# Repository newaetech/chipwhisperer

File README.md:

# ChipWhisperer

## Important Links

[Documentation](https://chipwhisperer.readthedocs.io/en/sca101/index.html) | [Labs](https://github.com/newaetech/chipwhisperer-jupyter/tree/sca101) | [Forum](http://forum.newae.com) | [Store](https://store.newae.com) | [NewAE](http://newae.com)

## ChipWhisperer 7.0: Revamped Analyzer, Project, SCA101

ChipWhisperer 7.0 is bringing major improvements to projects, analyzer, as well as a new online course, SCA101. These changes include:

* New Zarr based projects with improved functionality over previous projects
* New CPA attack class with major performance improvements
* Better results API for CPA attacks
* Simplification for project/analyzer API
* Use of integer math throughout the project
* Removal of unmaintained parts of Analyzer
* Porting of MixColumns attack to Analyzer
* Iterators for KTP classes

We also have a more thorough [document of changes](https://docs.google.com/document/d/1KBrlV3X3fyg3PniKdv6pZg0s0MAX2dzbSdZiwbm_nh4/edit?usp=sharing).

The [SCA101 Online course](https://learn.chipwhisperer.io/courses/sca101) is available at [learn.chipwhisperer.io](https://learn.chipwhisperer.io).

**If you need to use ChipWhisperer with the previous API, the final commit with that is available as tag v6.1.0**

## What is ChipWhisperer?

ChipWhisperer is an open source toolchain dedicated to hardware security research. This toolchain consists of several layers of open source components:
* __Hardware__: The ChipWhisperer uses a _capture_ board and a _target_ board. Schematics and PCB layouts for the ChipWhisperer-Husky capture board and a number of target boards are freely available.
* __Firmware__: Three separate pieces of firmware are used on the ChipWhisperer hardware. The capture board has a USB controller (in C) and an FPGA for high-speed captures (in Verilog) with open-source firmware. Also, the target device has its own firmware; this repository includes many firmware examples for different targets.
* __Software__: The ChipWhisperer software includes a Python API for talking to ChipWhisperer hardware (ChipWhisperer Capture) and a Python API 
for processing power traces from ChipWhisperer hardware (ChipWhisperer Analyzer). 

You'll find documentation for all of the above [here](https://chipwhisperer.readthedocs.io/en/develop/index.html).

## Getting Started
First time using ChipWhisperer? Go to our new [documentation site](https://chipwhisperer.readthedocs.io/en/develop/index.html) for all you need to know to get started with ChipWhisperer.

## Help!
Stuck? If you need a hand, there are a few places you can ask for help:
* The [NewAE Forum](https://forum.newae.com/) is full of helpful people that can point you in the right direction
* If you find a bug, let us know through the [issue tracker](https://github.com/newaetech/chipwhisperer/issues)

---

ChipWhisperer is a trademark of NewAE Technology Inc., registered in the US, Europe, and China.

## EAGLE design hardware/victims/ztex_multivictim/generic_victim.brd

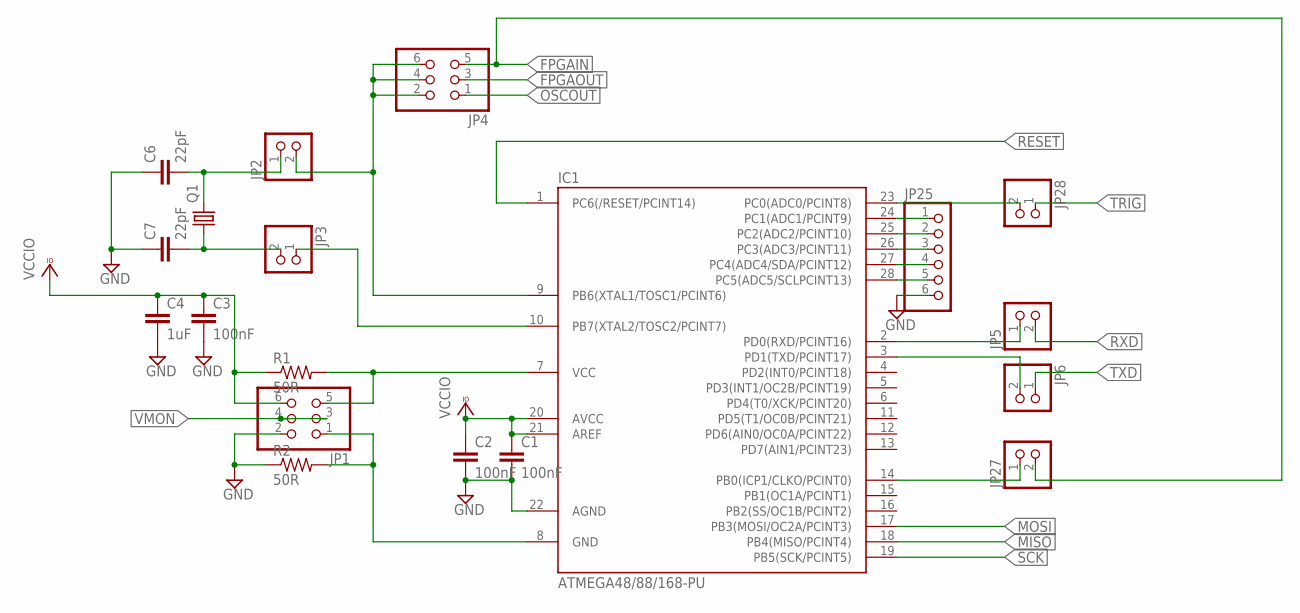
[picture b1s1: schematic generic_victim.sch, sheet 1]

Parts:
C1, C2, C3: 100nF; C0805
C4: 1uF; C0805
C6, C7: 22pF; C0805
IC1: ATMEGA48/88/168-PU; DIL28-3
JP1, JP4: PINHD-2X3; 2X03
JP2, JP3, JP5, JP6, JP27, JP28: PINHD-1X2; 1X02
JP25: PINHD-1X6; 1X06
Q1: CRYSTALHC49U70; HC49U70
R1, R2: 50R; R0805

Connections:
FPGAIN: JP4.5, JP27.2; also elsewhere on the board
FPGAOUT: JP4.3; also elsewhere on the board
GND: C1.2, C2.2, C3.2, C4.2, C6.1, C7.1, IC1.22 (AGND), JP1.2, JP25.6, R2.1; also elsewhere on the board
MISO: IC1.18 (PB4(MISO/PCINT4)); also elsewhere on the board
MOSI: IC1.17 (PB3(MOSI/OC2A/PCINT3)); also elsewhere on the board
unnamed: IC1.7 (VCC), JP1.5, R1.2
unnamed: IC1.8 (GND), JP1.1, R2.2
unnamed: IC1.10 (PB7(XTAL2/TOSC2/PCINT7)), JP3.1
unnamed: C7.2, JP3.2, Q1.1
unnamed: C6.2, JP2.1, Q1.2
unnamed: IC1.14 (PB0(ICP1/CLKO/PCINT0)), JP27.1
unnamed: IC1.2 (PD0(RXD/PCINT16)), JP5.1
unnamed: IC1.3 (PD1(TXD/PCINT17)), JP6.2
unnamed: IC1.9 (PB6(XTAL1/TOSC1/PCINT6)), JP2.2, JP4.2, JP4.4, JP4.6
unnamed: IC1.24 (PC1(ADC1/PCINT9)), JP25.1
unnamed: IC1.25 (PC2(ADC2/PCINT10)), JP25.2
unnamed: IC1.26 (PC3(ADC3/PCINT11)), JP25.3
unnamed: IC1.27 (PC4(ADC4/SDA/PCINT12)), JP25.4
unnamed: IC1.28 (PC5(ADC5/SCLPCINT13)), JP25.5
unnamed: IC1.23 (PC0(ADC0/PCINT8)), JP28.2
OSCOUT: JP4.1; also elsewhere on the board
RESET: IC1.1 (PC6(/RESET/PCINT14)); also elsewhere on the board
RXD: JP5.2; also elsewhere on the board
SCK: IC1.19 (PB5(SCK/PCINT5)); also elsewhere on the board
TRIG: JP28.1; also elsewhere on the board
TXD: JP6.1; also elsewhere on the board
VCCIO: C1.1, C2.1, C3.1, C4.1, IC1.20 (AVCC), IC1.21 (AREF), JP1.6, R1.1; also elsewhere on the board
VMON: JP1.3, JP1.4; also elsewhere on the board

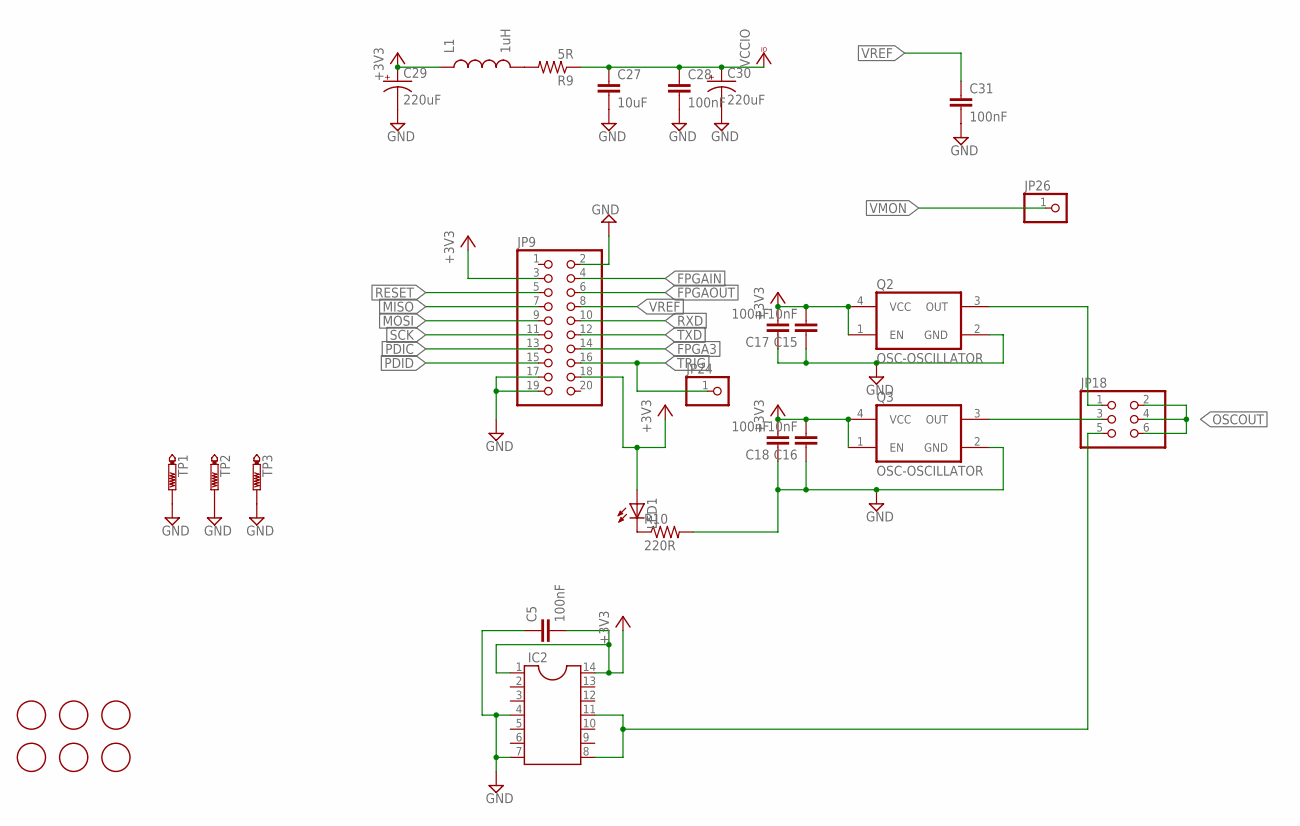
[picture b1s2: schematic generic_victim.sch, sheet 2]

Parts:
C5, C28, C31: 100nF; C0805
C15, C16: 10nF; C0603
C17, C18: 100nF; C0603
C27: 10uF; C0805
C29, C30: 220uF; E3,5-8
IC2: DIL14S; SOCKET-14
JP9: PINHD-2X10; 2X10
JP18: PINHD-2X3; 2X03
JP24, JP26: PINHD-1X1; 1X01
L1: 1uH; 0805
LED1: LED3MM
Q2, Q3: OSC-OSCILLATOR; OSCILLATOR_7X5_SMD
R9: 5R; R0805
R10: 220R; R0805
TP1, TP2, TP3: PTR1PAD1-13; P1-13
U$1, U$2, U$3, U$4, U$5, U$6: FIDUCIAL; FIDUCIAL_1MM

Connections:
+3V3: C5.2, C15.2, C16.2, C17.2, C18.2, C29.+, IC2.1, IC2.14, JP9.3, JP9.18, L1.1, LED1.A, Q2.1 (EN), Q2.4 (VCC), Q3.1 (EN), Q3.4 (VCC); also elsewhere on the board
FPGA3: JP9.14; also elsewhere on the board
FPGAIN: JP9.4; also elsewhere on the board
FPGAOUT: JP9.6; also elsewhere on the board
GND: C5.1, C15.1, C16.1, C17.1, C18.1, C27.2, C28.2, C29.-, C30.-, C31.2, IC2.4, IC2.7, JP9.2, JP9.17, JP9.19, Q2.2 (GND), Q3.2 (GND), R10.2, TP1.TP, TP2.TP, TP3.TP; also elsewhere on the board
MISO: JP9.7; also elsewhere on the board
MOSI: JP9.9; also elsewhere on the board
unnamed: IC2.8, IC2.11, JP18.5
unnamed: JP18.3, Q3.3 (OUT)
unnamed: JP18.1, Q2.3 (OUT)
unnamed: L1.2, R9.2
unnamed: LED1.K (C), R10.1
OSCOUT: JP18.2, JP18.4, JP18.6; also elsewhere on the board
PDIC: JP9.13; also elsewhere on the board
PDID: JP9.15; also elsewhere on the board
RESET: JP9.5; also elsewhere on the board
RXD: JP9.10; also elsewhere on the board
SCK: JP9.11; also elsewhere on the board
TRIG: JP9.16, JP24.1; also elsewhere on the board
TXD: JP9.12; also elsewhere on the board
VCCIO: C27.1, C28.1, C30.+, R9.1; also elsewhere on the board
VMON: JP26.1; also elsewhere on the board
VREF: C31.1, JP9.8; also elsewhere on the board

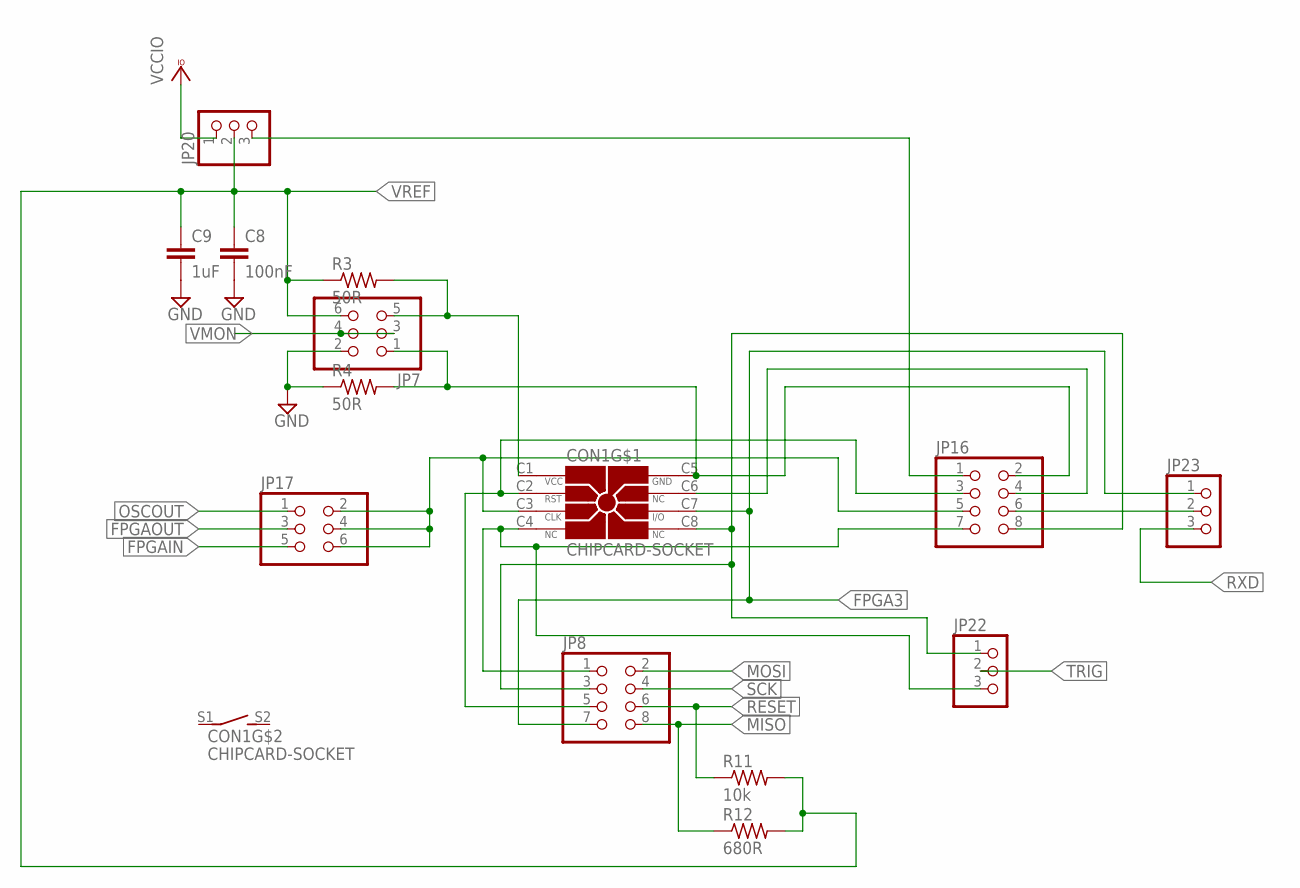
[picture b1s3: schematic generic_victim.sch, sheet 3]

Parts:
C8: 100nF; C0805
C9: 1uF; C0805
CON1: CHIPCARD-SOCKET; 7334L2622F05LF
JP7, JP17: PINHD-2X3; 2X03
JP8, JP16: PINHD-2X4; 2X04
JP20, JP22, JP23: PINHD-1X3; 1X03
R3, R4: 50R; R0805
R11: 10k; R0805
R12: 680R; R0805

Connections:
FPGA3: CON1.C7 (I/O), JP8.7, JP23.1; also elsewhere on the board
FPGAIN: JP17.5; also elsewhere on the board
FPGAOUT: JP17.3; also elsewhere on the board
GND: C8.2, C9.2, JP7.2, R4.1; also elsewhere on the board
MISO: JP8.8, R12.1; also elsewhere on the board
MOSI: JP8.2; also elsewhere on the board
unnamed: CON1.C4 (NC), JP8.1, JP16.7, JP22.3
unnamed: CON1.C1 (VCC), JP7.5, R3.2
unnamed: CON1.C2 (RST), JP8.5, JP16.3
unnamed: CON1.C5 (GND), JP7.1, JP16.2, R4.2
unnamed: CON1.C8 (NC), JP8.3, JP16.8, JP22.1
unnamed: JP16.6, JP23.2
unnamed: CON1.C6 (NC), JP16.4
unnamed: CON1.C3 (CLK), JP16.5, JP17.2, JP17.4, JP17.6
unnamed: JP16.1, JP20.3
OSCOUT: JP17.1; also elsewhere on the board
RESET: JP8.6, R11.1; also elsewhere on the board
RXD: JP23.3; also elsewhere on the board
SCK: JP8.4; also elsewhere on the board
TRIG: JP22.2; also elsewhere on the board
VCCIO: JP20.1; also elsewhere on the board
VMON: JP7.3, JP7.4; also elsewhere on the board
VREF: C8.1, C9.1, JP7.6, JP20.2, R3.1, R11.2, R12.2; also elsewhere on the board

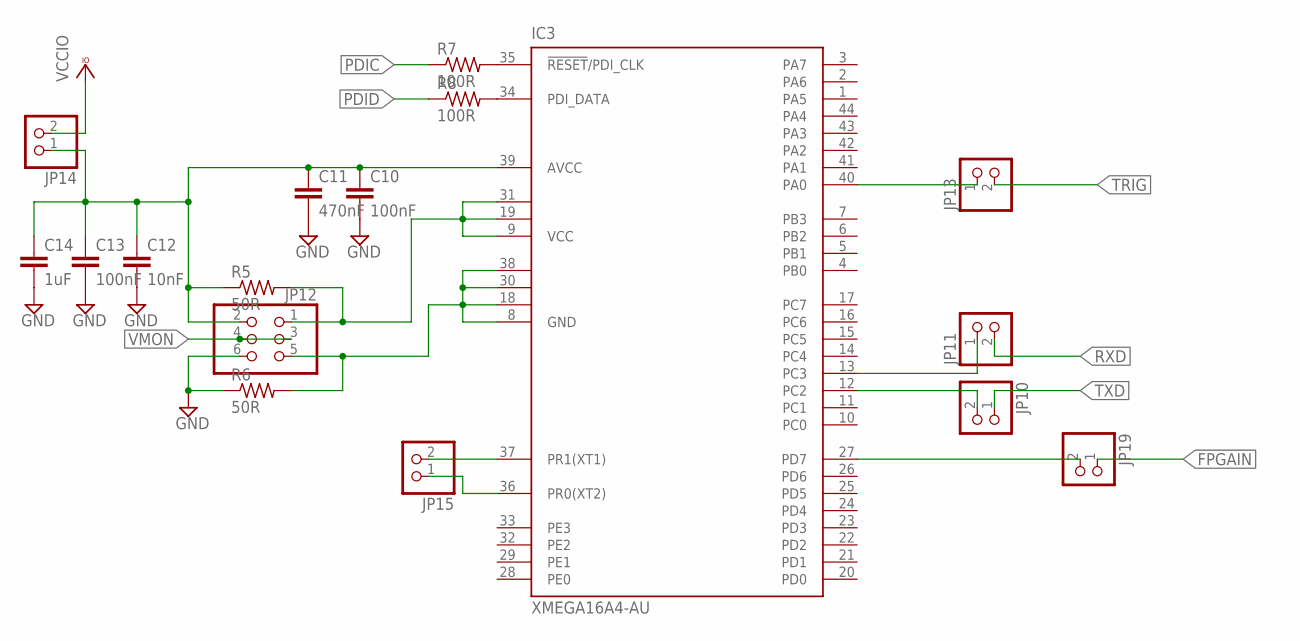
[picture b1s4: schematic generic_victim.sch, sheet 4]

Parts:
C10, C13: 100nF; C0805
C11: 470nF; C0805
C12: 10nF; C0805
C14: 1uF; C0805
IC3: XMEGA16A4-AU; TQFP44
JP10, JP11, JP13, JP14, JP15, JP19: PINHD-1X2; 1X02
JP12: PINHD-2X3; 2X03
R5, R6: 50R; R0805
R7, R8: 100R; M0805

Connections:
FPGAIN: JP19.1; also elsewhere on the board
GND: C10.2, C11.2, C12.2, C13.2, C14.2, JP12.6, R6.1; also elsewhere on the board
unnamed: IC3.13 (PC3), JP11.1
unnamed: IC3.12 (PC2), JP10.2
unnamed: IC3.27 (PD7), JP19.2
unnamed: C10.1, C11.1, C12.1, C13.1, C14.1, IC3.39 (AVCC), JP12.2, JP14.1, R5.1
unnamed: IC3.35 (!RESET!/PDI_CLK), R7.2
unnamed: IC3.34 (PDI_DATA), R8.2
unnamed: IC3.40 (PA0), JP13.1
unnamed: IC3.9 (VCC), IC3.19 (VCC1), IC3.31 (VCC2), JP12.1, R5.2
unnamed: IC3.8 (GND), IC3.18 (GND1), IC3.30 (GND2), IC3.38 (GND3), JP12.5, R6.2
unnamed: IC3.37 (PR1(XT1)), JP15.2
unnamed: IC3.36 (PR0(XT2)), JP15.1
PDIC: R7.1; also elsewhere on the board
PDID: R8.1; also elsewhere on the board
RXD: JP11.2; also elsewhere on the board
TRIG: JP13.2; also elsewhere on the board
TXD: JP10.1; also elsewhere on the board
VCCIO: JP14.2; also elsewhere on the board
VMON: JP12.3, JP12.4; also elsewhere on the board

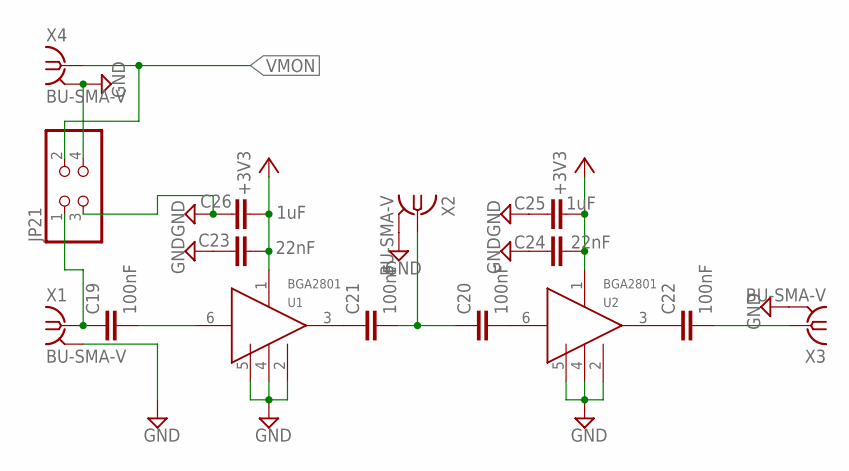
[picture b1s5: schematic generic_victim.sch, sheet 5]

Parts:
C19, C20, C21, C22: 100nF; C0603
C23, C24: 22nF; C0603
C25, C26: 1uF; C0603
JP21: PINHD-2X2; 2X02
U1, U2: BGA2801; SOTT323-6
X1, X2, X3, X4: BU-SMA-V

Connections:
+3V3: C23.2, C24.2, C25.2, C26.2, U1.1 (VCC), U2.1 (VCC); also elsewhere on the board
GND: C23.1, C24.1, C25.1, C26.1, JP21.3, JP21.4, U1.2 (GND), U1.4 (GND), U1.5 (GND), U2.2 (GND), U2.4 (GND), U2.5 (GND), X1.2, X1.3 (2), X1.4 (2), X1.5 (2), X2.2, X2.3 (2), X2.4 (2), X2.5 (2), X3.2, X3.3 (2), X3.4 (2), X3.5 (2), X4.2, X4.3 (2), X4.4 (2), X4.5 (2); also elsewhere on the board
unnamed: C19.1, JP21.1, X1.1
unnamed: C22.2, X3.1
unnamed: C22.1, U2.3 (OUT)
unnamed: C21.1, U1.3 (OUT)
unnamed: C20.2, U2.6 (IN)
unnamed: C19.2, U1.6 (IN)
unnamed: C20.1, C21.2, X2.1
VMON: JP21.2, X4.1; also elsewhere on the board

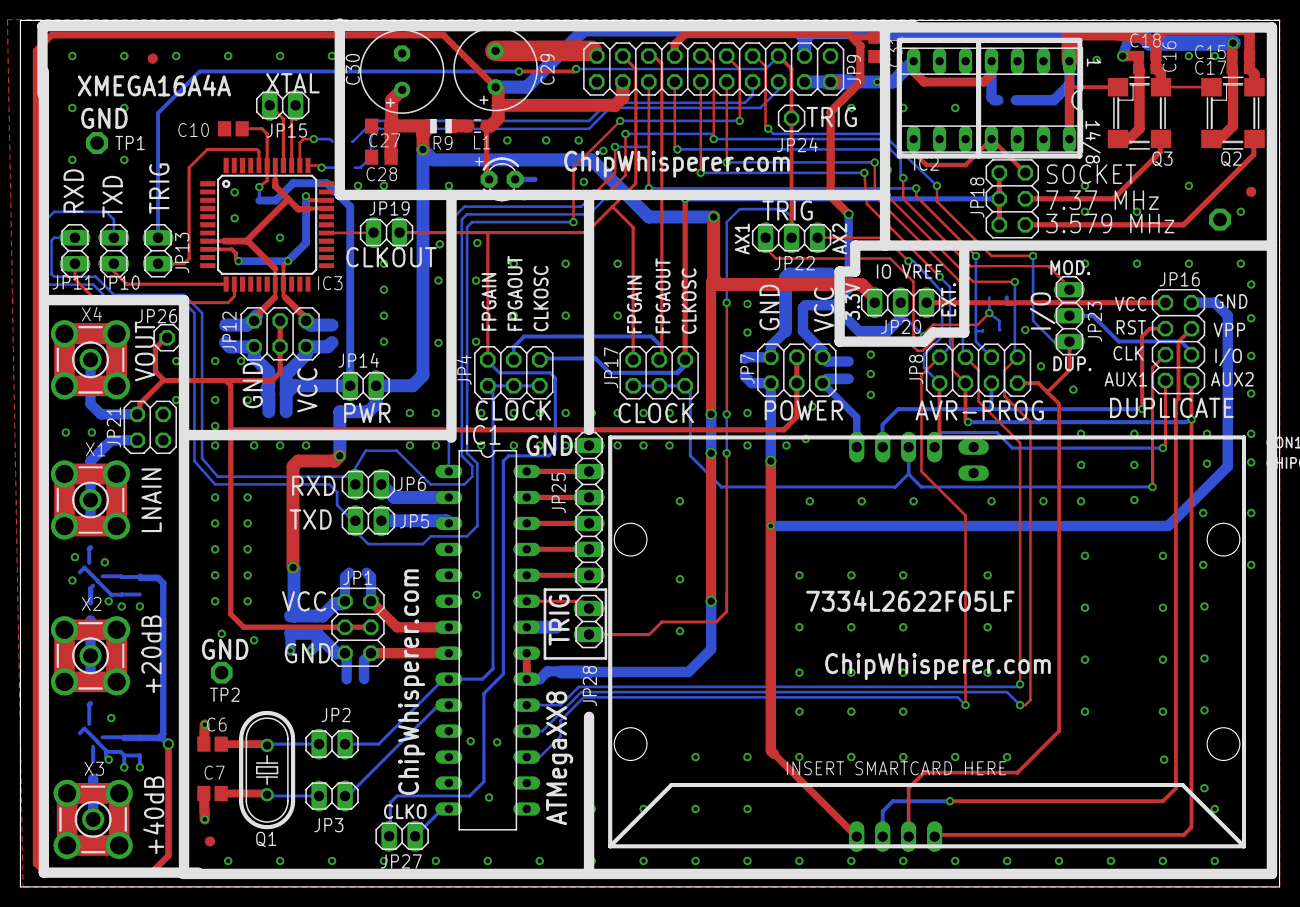
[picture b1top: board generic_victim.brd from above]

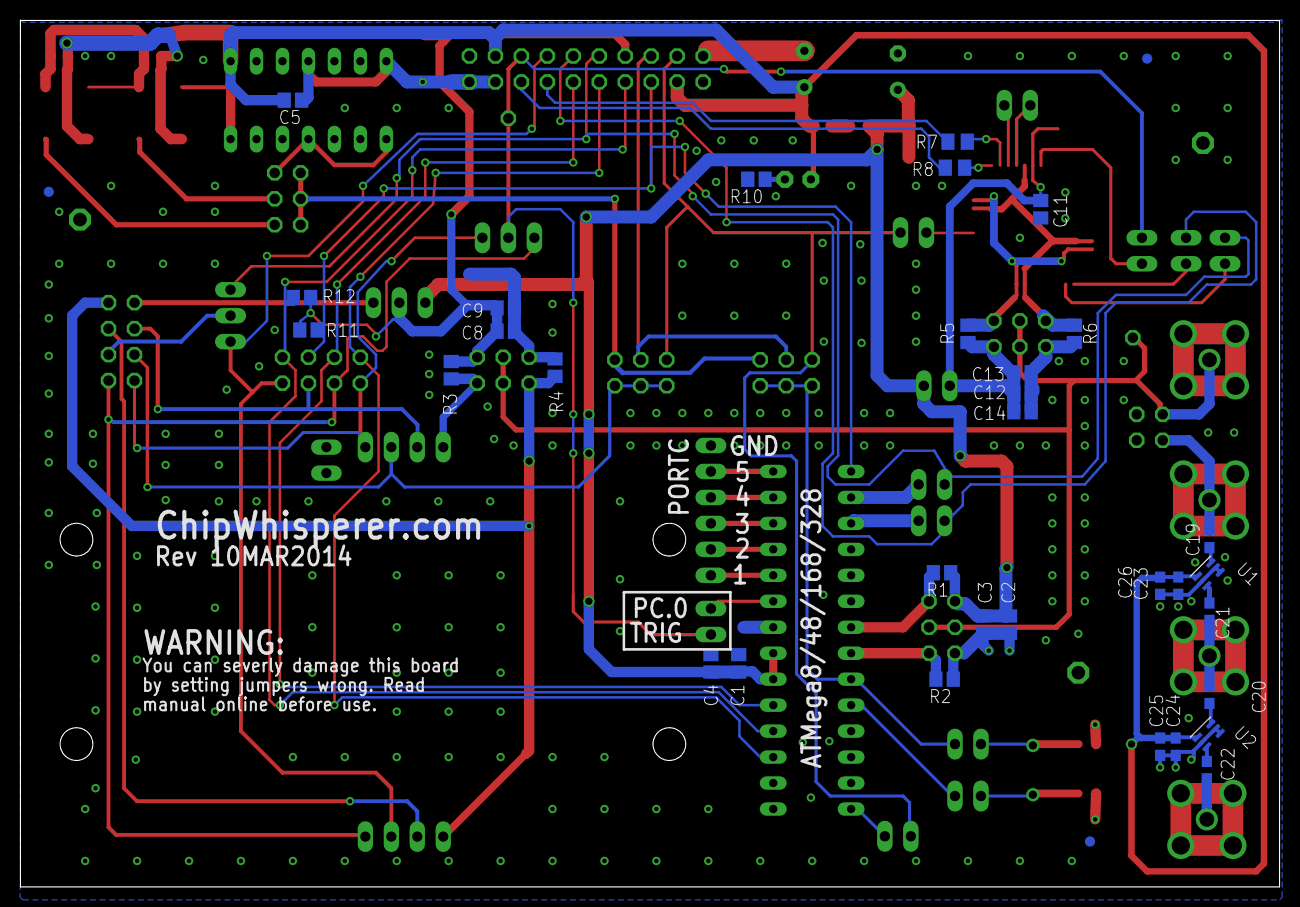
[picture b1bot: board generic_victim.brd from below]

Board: 2 copper layers, 123.2 x 84.8 mm, 95 parts (35 on the bottom side), 65 nets.

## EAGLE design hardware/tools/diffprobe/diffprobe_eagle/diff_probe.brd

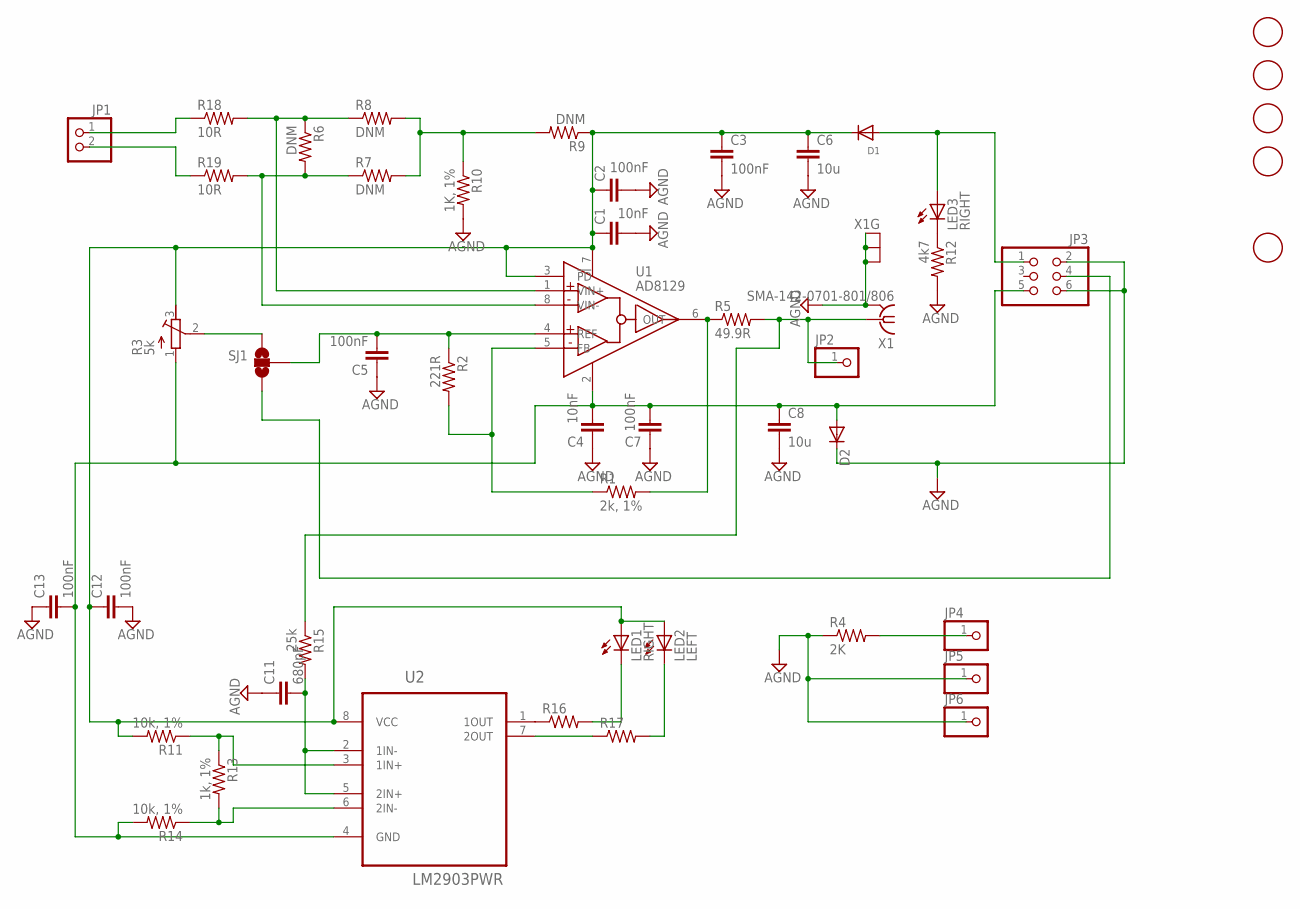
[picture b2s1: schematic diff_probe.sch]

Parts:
C1, C4: 10nF; C0603
C2, C3, C5, C7: 100nF; C0603
C6, C8: 10u; C0805
C11: 680pF; C0402
C12, C13: 100nF; C0402
D1: DIODESOD-123; SOD-123
D2: DIODE-DO-214AC; DO-214AC
FID1, FID2, FID4, FID5, FID6: FIDUCIAL; FIDUCIAL_1MM
JP1: PINHD-1X2/90; 1X02/90
JP2, JP4, JP5, JP6: PINHD-1X1; 1X01
JP3: PINHD-2X3EDGE; 6PAD_ISP
LED1, LED3: RIGHT; CHIPLED_0603
LED2: LEFT; CHIPLED_0603
R1: 2k, 1%; R0603
R2: 221R; R0603
R3: 5k; RTRIM3224J
R4: 2K; R0603
R5: 49.9R; R0603
R6: DNM; M0805
R7, R8, R9: DNM; R0603
R10: 1K, 1%; R0603
R11, R14: 10k, 1%; R0402
R12: 4k7; R0603
R13: 1k, 1%; R0402
R15: 25k; R0402
R16, R17: R-US_R0402; R0402
R18, R19: 10R; R0603
SJ1: SOLDERJUMPER_2WAYPASTE1&2; SJ_3_PASTE1&2
U1: AD8129; SO08
U2: LM2903PWR; SOP65P640X120-8N
X1: SMA-142-0701-801/806; J502-ND-142-0701-801/806

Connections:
AGND: C1.2, C2.2, C3.2, C4.1, C5.1, C6.2, C7.1, C8.2, C11.1, C12.2, C13.1, D2.C, JP3.2 (1), JP3.6 (5), JP5.1, JP6.1, R4.1, R10.2, R12.2, X1.G@1 (GND), X1.G@2 (GND), X1.G@3 (GND), X1.G@4 (GND)
unnamed: D1.A, JP3.1 (2), LED3.A
unnamed: C1.1, C2.1, C3.1, C6.1, C12.1, D1.C, LED1.A, LED2.A, R3.3 (A), R9.1, R11.2, U1.3 (!PD), U1.7 (VCC), U2.8 (VCC)
unnamed: C5.2, R2.1, SJ1.2, U1.4 (REF)
unnamed: R1.1, R2.2, U1.5 (FB)
unnamed: R1.2, R5.1, U1.6 (OUT)
unnamed: JP1.1, R18.1
unnamed: R6.1, R8.1, R18.2, U1.1 (VIN+)
unnamed: C4.2, C7.2, C8.1, C13.2, D2.A, JP3.5 (6), R3.1 (E), R14.2, U1.2 (VSS), U2.4 (GND)
unnamed: LED3.C, R12.1
unnamed: JP3.4 (3), SJ1.3
unnamed: JP4.1, R4.2
unnamed: JP2.1, R5.2, R15.1, X1.1
unnamed: R6.2, R7.1, R19.2, U1.8 (VIN-)
unnamed: JP1.2, R19.1
unnamed: R7.2, R8.2, R9.2, R10.1
unnamed: R11.1, R13.1, U2.3 (1IN+)
unnamed: R13.2, R14.1, U2.6 (2IN-)
unnamed: R16.1, U2.1 (1OUT)
unnamed: C11.2, R15.2, U2.2 (1IN-), U2.5 (2IN+)
unnamed: LED1.C, R16.2
unnamed: R17.1, U2.7 (2OUT)
unnamed: LED2.C, R17.2
unnamed: R3.2 (S), SJ1.1

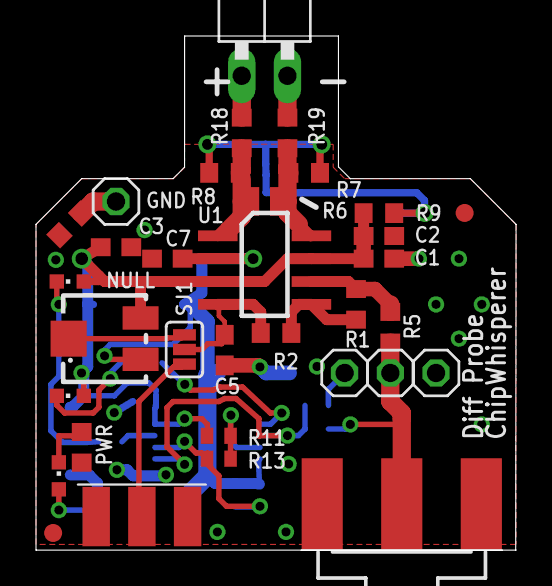
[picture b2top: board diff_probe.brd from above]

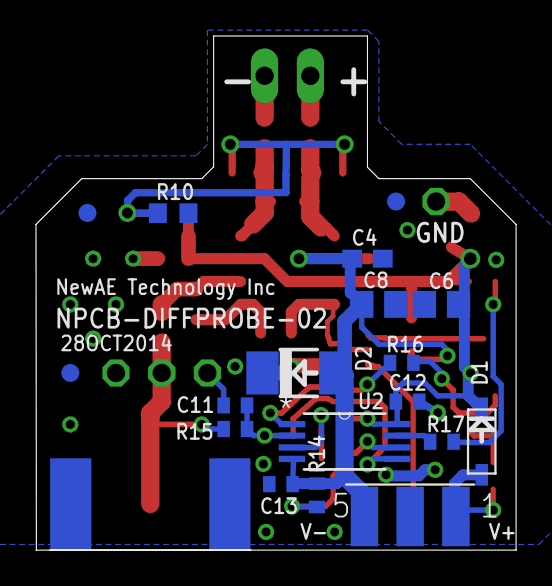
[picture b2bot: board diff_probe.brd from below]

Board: 2 copper layers, 26.7 x 28.6 mm, 50 parts (17 on the bottom side), 24 nets.

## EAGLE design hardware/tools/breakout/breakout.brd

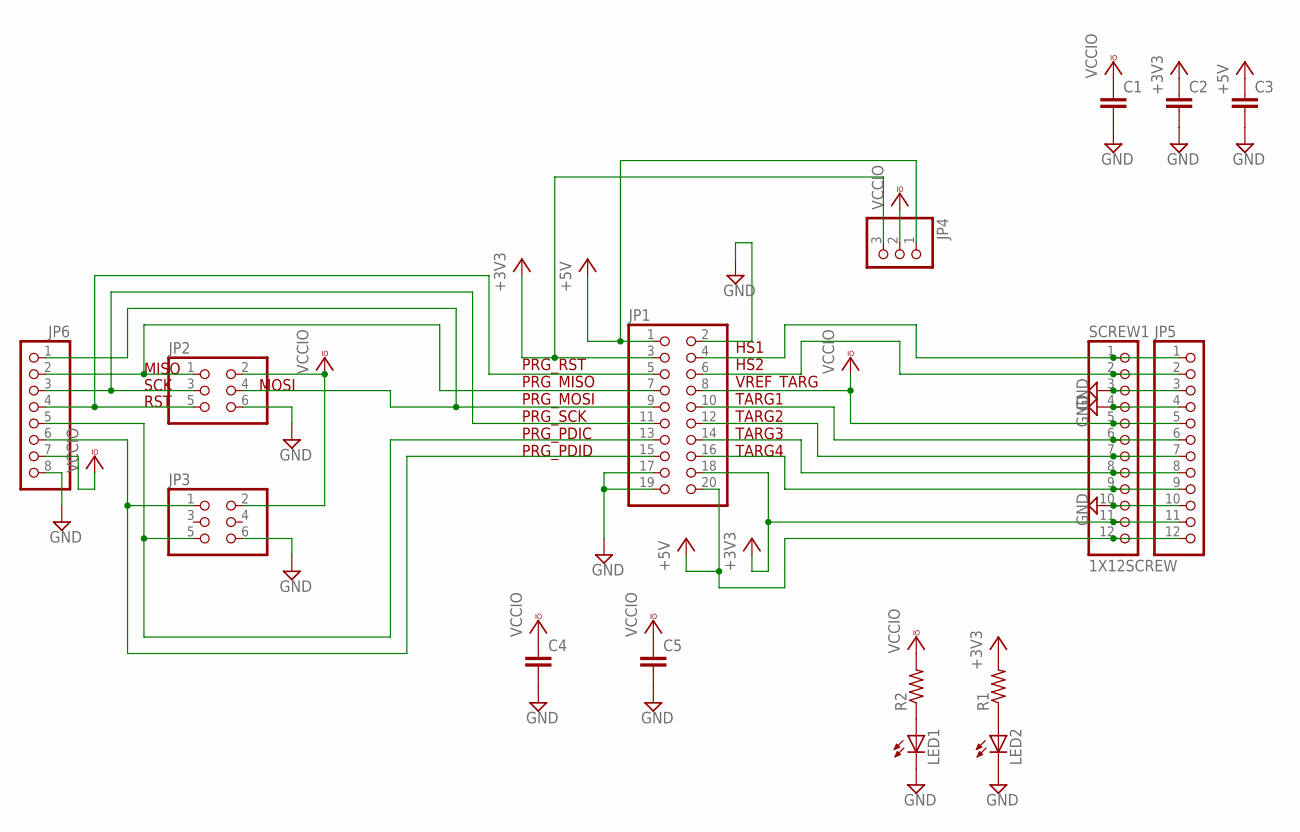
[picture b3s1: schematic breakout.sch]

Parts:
C1, C2, C3, C4, C5: C-EUC0805; C0805
JP1: PINHD-2X10; 2X10
JP2, JP3: PINHD-2X3; 2X03
JP4: PINHD-1X3; 1X03
JP5: PINHD-1X12; 1X12
JP6: PINHD-1X8; 1X08
LED1, LED2: LED3MM
R1, R2: R-US_R0805; R0805
SCREW1: 1X12SCREW; 1X12_SCREW

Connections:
+3V3: C2.1, JP1.3, JP1.18, JP4.3, JP5.11, R1.2, SCREW1.11
+5V: C3.1, JP1.1, JP1.20, JP4.1, JP5.12, SCREW1.12
GND: C1.2, C2.2, C3.2, C4.2, C5.2, JP1.2, JP1.17, JP1.19, JP2.6, JP3.6, JP5.3, JP5.4, JP5.10, JP6.8, LED1.K (C), LED2.K (C), SCREW1.3, SCREW1.4, SCREW1.10
MISO: JP1.7, JP2.1, JP6.2
MOSI: JP1.9, JP2.4, JP6.1
unnamed: LED2.A, R1.1
unnamed: LED1.A, R2.1
unnamed: JP1.4, JP5.1, SCREW1.1
unnamed: JP1.15, JP3.1, JP6.6
unnamed: JP1.13, JP3.5, JP6.5
unnamed: JP1.6, JP5.2, SCREW1.2
unnamed: JP1.10, JP5.6, SCREW1.6
unnamed: JP1.12, JP5.7, SCREW1.7
unnamed: JP1.14, JP5.8, SCREW1.8
unnamed: JP1.16, JP5.9, SCREW1.9
RST: JP1.5, JP2.5, JP6.4
SCK: JP1.11, JP2.3, JP6.3
VCCIO: C1.1, C4.1, C5.1, JP1.8, JP2.2, JP3.2, JP4.2, JP5.5, JP6.7, R2.2, SCREW1.5

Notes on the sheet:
HS1 HS2 VREF_TARG TARG1 TARG2 TARG3 TARG4
PRG_RST PRG_MISO PRG_MOSI PRG_SCK PRG_PDIC PRG_PDID
MISO
SCK
RST
MOSI

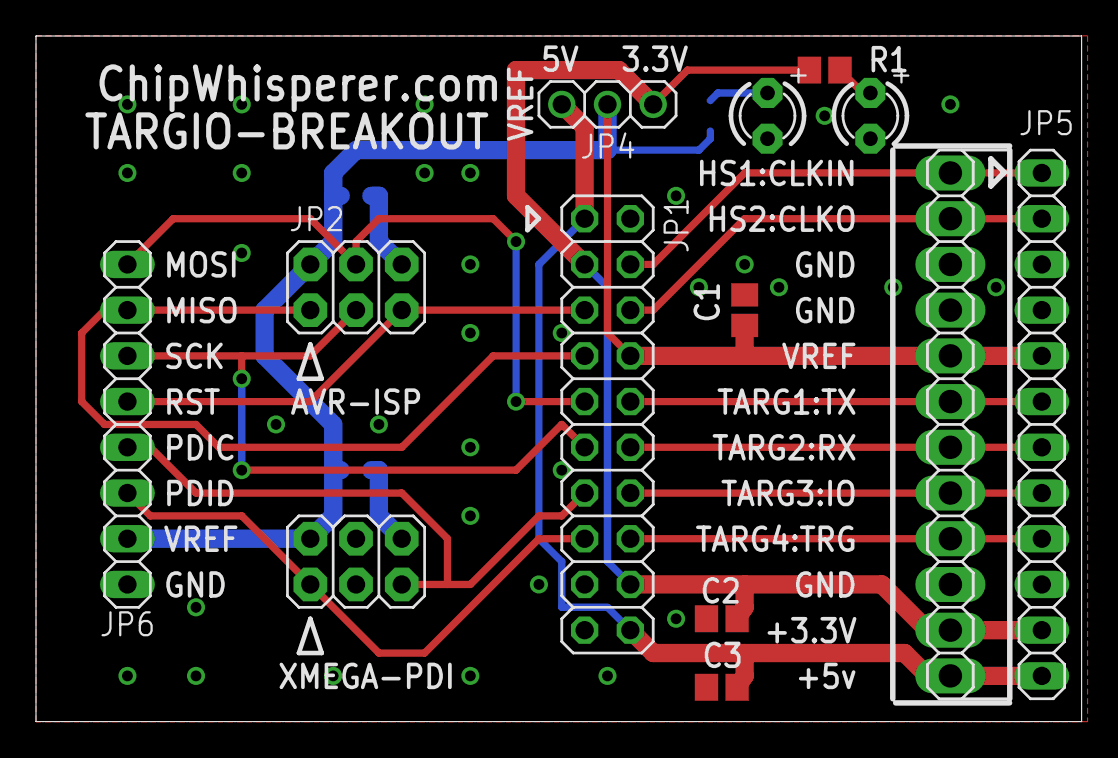
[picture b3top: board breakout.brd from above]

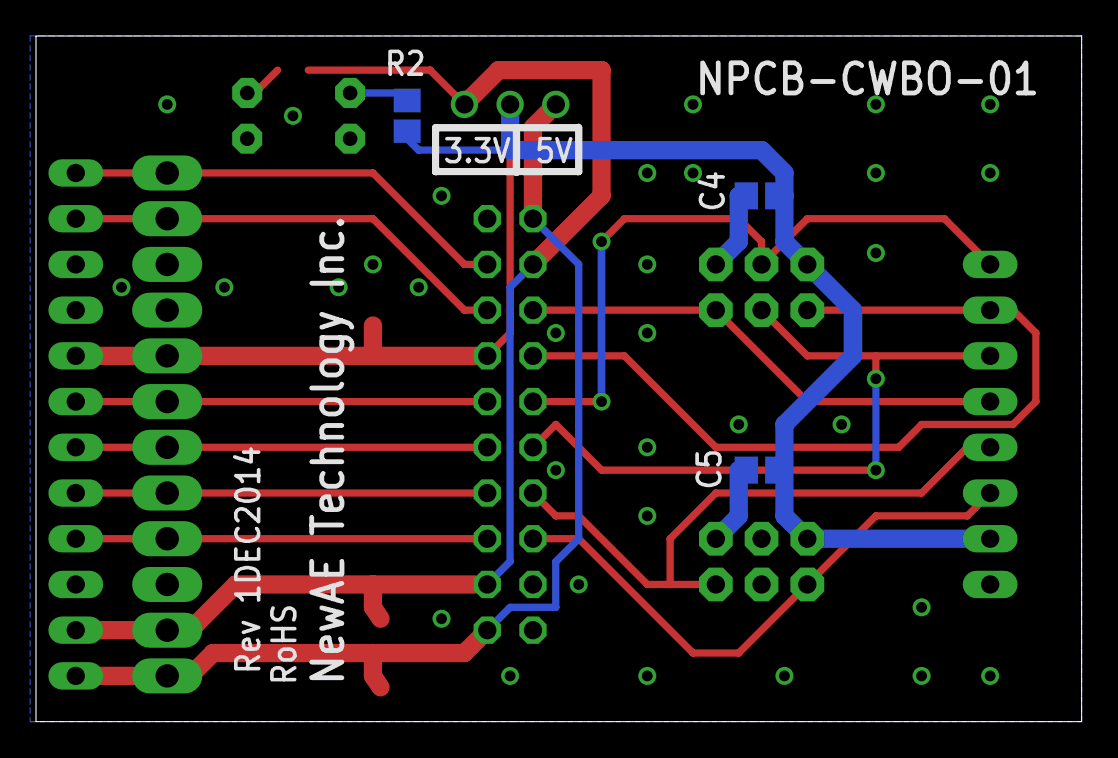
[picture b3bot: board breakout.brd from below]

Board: 2 copper layers, 58.1 x 38.1 mm, 16 parts (3 on the bottom side), 18 nets.

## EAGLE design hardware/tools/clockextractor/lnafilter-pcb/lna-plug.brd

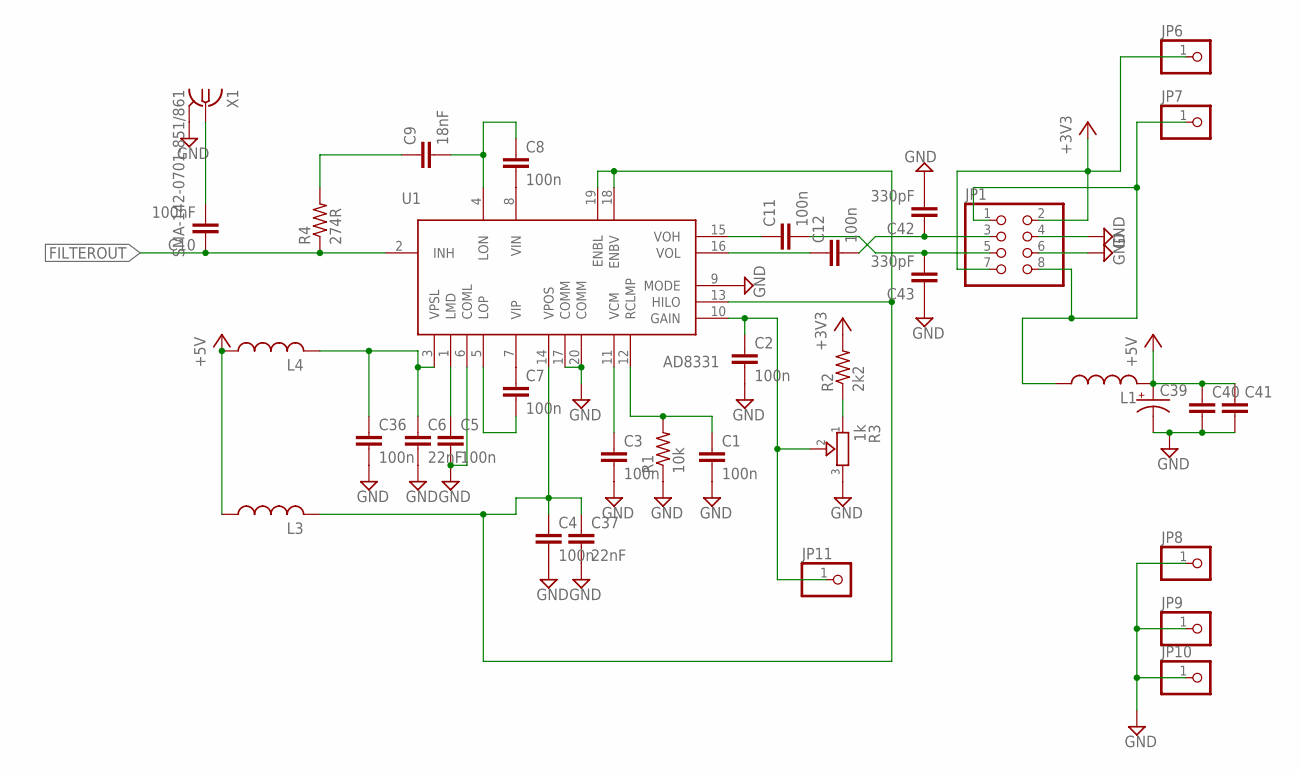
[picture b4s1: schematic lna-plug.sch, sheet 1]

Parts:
C1, C2, C3, C4, C5, C7, C8, C11, C12, C36: 100n; C0603
C6, C37: 22nF; C0603
C9: 18nF; C0603
C10: 100nF; C0603
C39: CPOL-USSMCC; SMC_C
C40: C-EUC1206; C1206
C41: C-EUC0805; C0805
C42, C43: 330pF; C0603
JP1: PINHD-2X4; 2X04
JP6, JP7, JP8, JP9, JP10, JP11: PINHD-1X1; 1X01
L1, L3, L4: L-USL2012C; L2012C
R1: 10k; R0603
R2: 2k2; R0603
R3: 1k; TRIMMER_3362P
R4: 274R; R0603
U1: AD8331; QSOP20
X1: SMA-142-0701-851/861; J502-ND-142-0701-851/861

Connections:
+3V3: JP1.2, JP1.7, JP6.1, R2.2; also elsewhere on the board
+5V: C39.+, C40.1, C41.1, L1.2, L3.1, L4.1
FILTEROUT: C10.1, R4.1, U1.2 (INH); also elsewhere on the board
GND: C1.2, C2.2, C3.2, C4.2, C5.2, C6.2, C36.2, C37.2, C39.-, C40.2, C41.2, C42.2, C43.1, JP1.4, JP1.6, JP8.1, JP9.1, JP10.1, R1.1, R3.3, U1.6 (COML), U1.9 (MODE), U1.17 (COMM), U1.20 (COMM), X1.G@1 (2), X1.G@2 (2), X1.G@3 (2), X1.G@4 (2); also elsewhere on the board
unnamed: C7.1, U1.7 (VIP)
unnamed: C8.2, U1.8 (VIN)
unnamed: C8.1, C9.2, U1.4 (LON)
unnamed: C7.2, U1.5 (LOP)
unnamed: C3.1, U1.11 (VCM)
unnamed: C1.1, R1.2, U1.12 (RCLMP)
unnamed: C2.1, JP11.1, R3.2, U1.10 (GAIN)
unnamed: R2.1, R3.1
unnamed: C5.1, U1.1 (LMD)
unnamed: C6.1, C36.1, L4.2, U1.3 (VPSL)
unnamed: C9.1, R4.2
unnamed: C12.1, U1.16 (VOL)
unnamed: C11.1, U1.15 (VOH)
unnamed: C12.2, C42.1, JP1.3
unnamed: C11.2, C43.2, JP1.5
unnamed: JP1.1, JP1.8, JP7.1, L1.1
unnamed: C10.2, X1.1
unnamed: C4.1, C37.1, L3.2, U1.13 (HILO), U1.14 (VPOS), U1.18 (ENBV), U1.19 (ENBL)

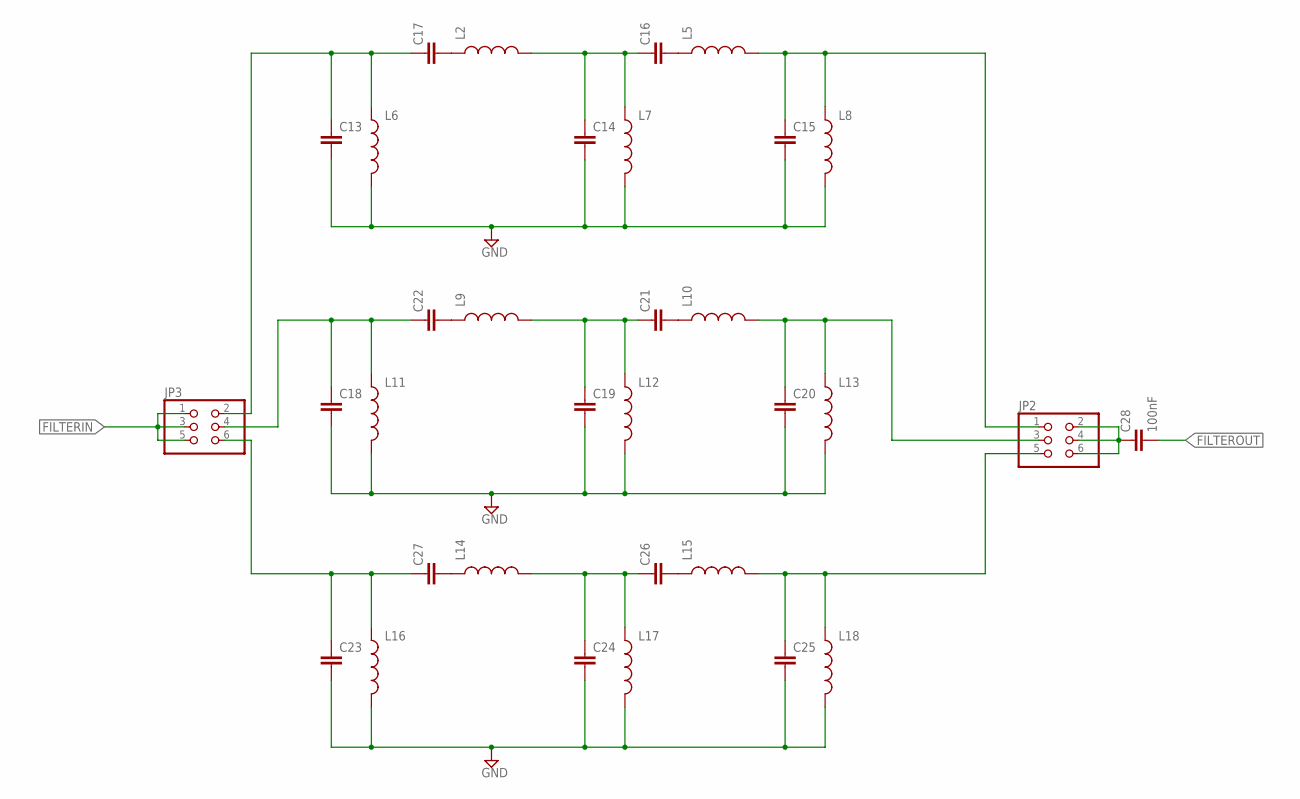
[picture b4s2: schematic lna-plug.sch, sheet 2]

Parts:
C13, C14, C15, C16, C17, C18, C19, C20, C21, C22, C23, C24, C25, C26, C27: C-EUC0603; C0603
C28: 100nF; C0603
JP2, JP3: PINHD-2X3; 2X03
L2, L5, L6, L7, L8, L9, L10, L11, L12, L13, L14, L15, L16, L17, L18: INDUCTOR0603; 0603

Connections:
FILTERIN: JP3.1, JP3.3, JP3.5; also elsewhere on the board
FILTEROUT: C28.2; also elsewhere on the board
GND: C13.2, C14.2, C15.2, C18.2, C19.2, C20.2, C23.2, C24.2, C25.2, L6.2, L7.2, L8.2, L11.2, L12.2, L13.2, L16.2, L17.2, L18.2; also elsewhere on the board
unnamed: C17.2, L2.1
unnamed: C16.2, L5.1
unnamed: C14.1, C16.1, L2.2, L7.1
unnamed: C15.1, JP2.1, L5.2, L8.1
unnamed: C23.1, C27.1, JP3.6, L16.1
unnamed: C22.2, L9.1
unnamed: C21.2, L10.1
unnamed: C19.1, C21.1, L9.2, L12.1
unnamed: C25.1, JP2.5, L15.2, L18.1
unnamed: C18.1, C22.1, JP3.4, L11.1
unnamed: C27.2, L14.1
unnamed: C26.2, L15.1
unnamed: C24.1, C26.1, L14.2, L17.1
unnamed: C28.1, JP2.2, JP2.4, JP2.6
unnamed: C13.1, C17.1, JP3.2, L6.1
unnamed: C20.1, JP2.3, L10.2, L13.1

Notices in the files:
esp_prog.py:
Copyright (C) 2014-2016 Fredrik Ahlberg, Angus Gratton, Espressif Systems (Shanghai) PTE LTD, other contributors as noted.
This program is free software; you can redistribute it and/or modify it under
the terms of the GNU General Public License as published by the Free Software
firmware/mcu/hal/aurix/IfxScu_regdef.h:
\copyright Copyright (c) 2014 Infineon Technologies AG. All rights reserved.
hardware/capture/chipwhisperer-lite/pcb/eagle/cw-lite-main.brd:
Copyright NewAE Technology Inc.
hardware/victims/cw304_notduino/cw304_notduino_02.brd:
Copyright 2015
